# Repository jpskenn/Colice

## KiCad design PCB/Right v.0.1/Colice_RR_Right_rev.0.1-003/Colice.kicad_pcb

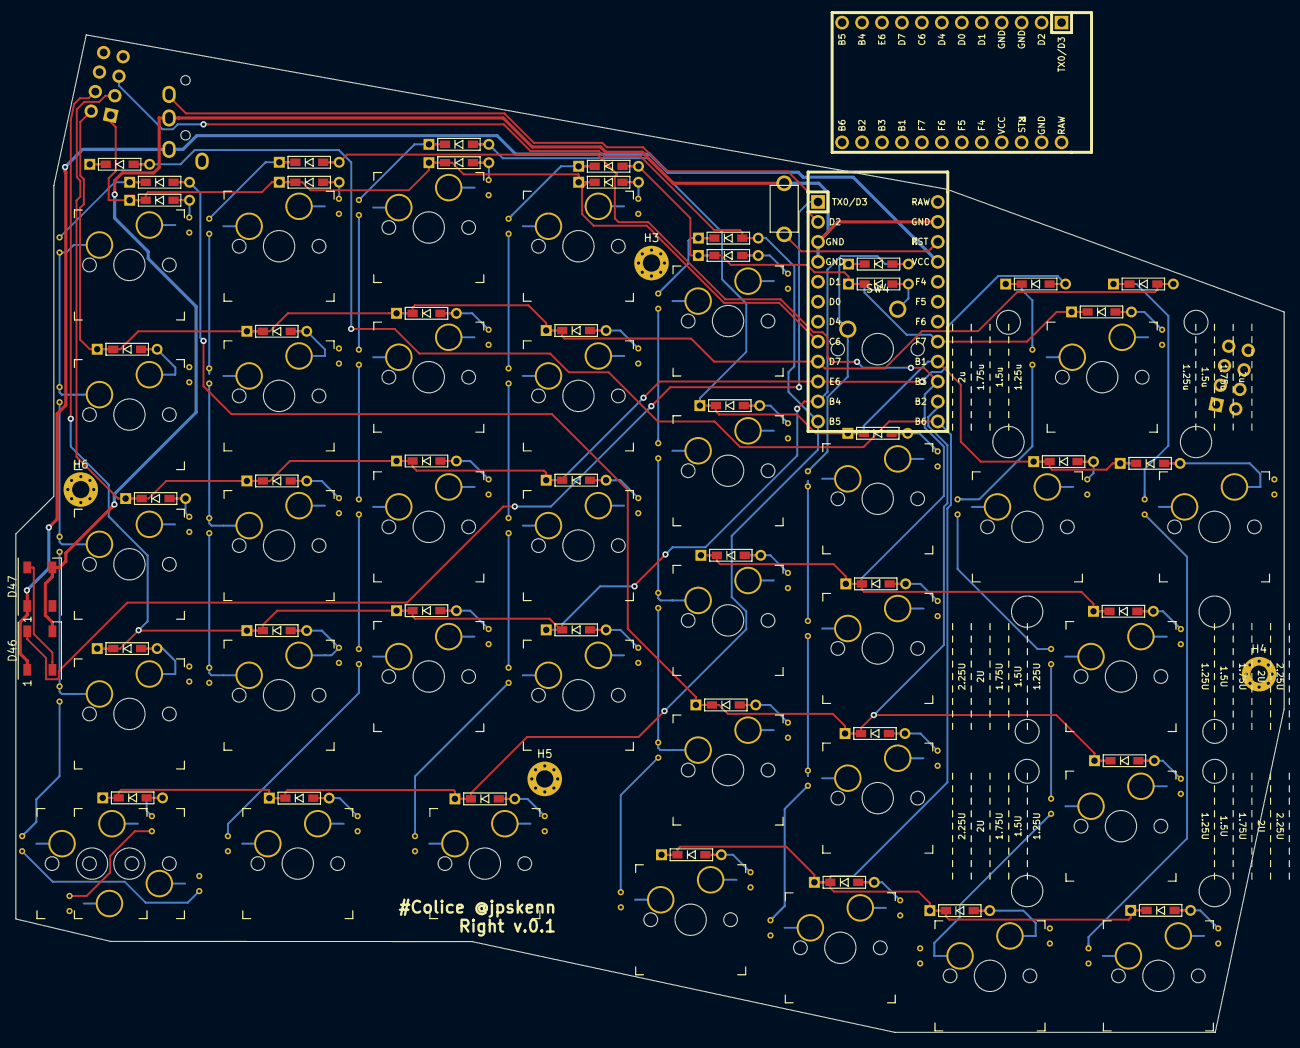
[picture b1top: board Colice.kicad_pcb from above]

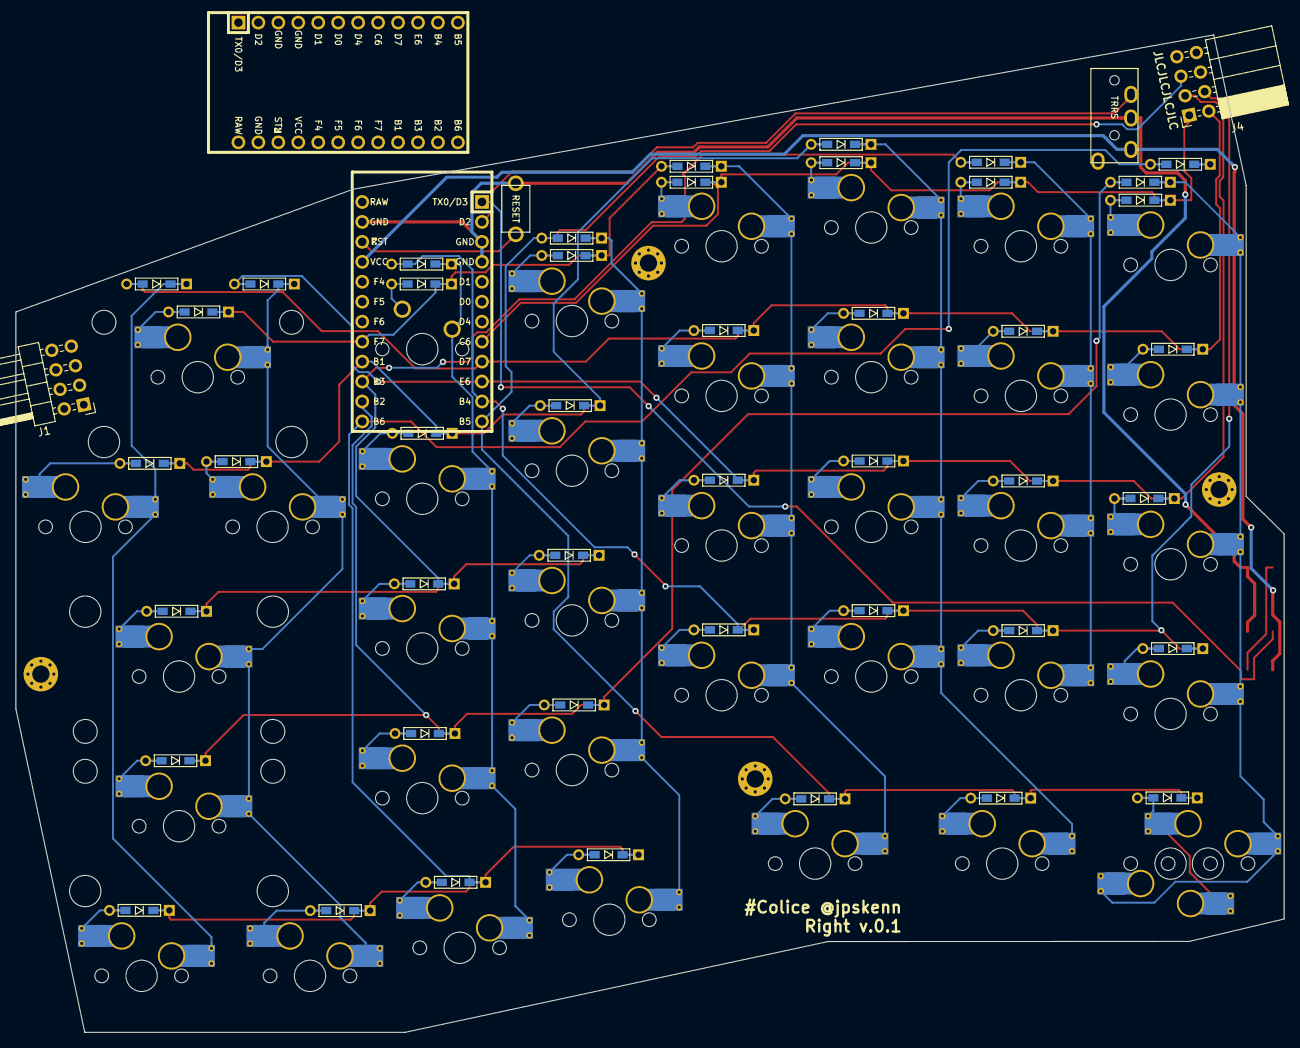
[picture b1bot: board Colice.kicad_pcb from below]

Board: 2 copper layers, 161.4 x 127.0 mm, 97 parts (5 on the bottom side), 60 nets.

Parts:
D1, D2, D3, D4, D5, D6, D7, D8, D9, D10, D11, D12, D13, D14, D15, D16, D17, D18, D19, D20, D21, D22, D23, D24, D25, D26, D27, D28, D29, D30, D31, D32, D34, D35, D36, D37, D38, D40, D45, D48, D49, D50, D51, D52, D53: D; D3_TH_SMD
D46, D47: WS2812B; LED_WS2812B_PLCC4_5.0x5.0mm_P3.2mm
H2: MountingHole; CherryMX_MidHeight_Choc_Hotswap_2U_Outline
H3, H4, H5, H6: MountingHole; MountingHole_2.2mm_M2_Pad_Via
H7, H8: MountingHole; CherryMX_MidHeight_Choc_Hotswap_2.25U_Outline
J1: Conn_02x04_Counter_Clockwise; PinHeader_2x04_P2.54mm_Horizontal
J3: MJ-4PP-9
J4: Conn_02x04_Counter_Clockwise; PinSocket_2x04_P2.54mm_Horizontal
SW1: SW_Push; ResetSW
SW3, SW5, SW6, SW7, SW8, SW9, SW10, SW11, SW12, SW14, SW15, SW16, SW17, SW18, SW19, SW20, SW21, SW22, SW23, SW24, SW25, SW26, SW27, SW29, SW30, SW31, SW32, SW33, SW38, SW39, SW40, SW41, SW42, SW43, SW44, SW45: SW_Push; CherryMX_Hotswap_v2
SW4: SW_Push; SW_Cherry_MX1A_1.00u_PCB
U1, U1#2: ProMicro; ArduinoProMicro

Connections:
GND1: D46.3, D47.3, J3.C, SW1.2, U1#2.3, U1#2.4, U1#2.23
unnamed: D1.1, SW3.1, SW41.1, SW42.1, SW43.1, SW44.1
unnamed: D2.2, SW41.2
unnamed: D3.2, SW3.2
unnamed: D4.1, SW4.1, SW5.1, SW6.1, SW7.1, SW8.1
unnamed: D5.2, SW4.2
unnamed: D6.2, SW5.2
unnamed: D7.2, SW6.2
unnamed: D8.2, SW7.2
unnamed: D9.2, SW8.2
unnamed: D10.1, SW9.1, SW10.1, SW11.1, SW12.1, SW45.1
unnamed: D11.2, SW9.2
unnamed: D12.2, SW10.2
unnamed: D13.2, SW11.2
unnamed: D14.2, SW12.2
unnamed: D15.1, SW39.1, SW40.1
unnamed: D16.1, SW14.1, SW15.1, SW16.1, SW17.1, SW18.1
unnamed: D17.2, SW14.2
unnamed: D18.2, SW15.2
unnamed: D19.2, SW16.2
unnamed: D20.2, SW17.2
unnamed: D21.2, SW18.2
unnamed: D22.1, SW19.1, SW20.1, SW21.1, SW22.1, SW23.1
unnamed: D23.2, SW19.2
unnamed: D24.2, SW20.2
unnamed: D25.2, SW21.2
unnamed: D26.2, SW22.2
unnamed: D27.2, SW23.2
unnamed: D28.1, SW24.1, SW25.1, SW26.1, SW27.1
unnamed: D29.2, SW24.2
unnamed: D30.2, SW25.2
unnamed: D31.2, SW26.2
unnamed: D32.2, SW27.2
unnamed: D34.1, SW29.1, SW30.1, SW31.1, SW32.1, SW33.1, SW38.1
unnamed: D35.2, SW29.2
unnamed: D36.2, SW30.2
unnamed: D37.2, SW31.2
unnamed: D38.2, SW32.2
unnamed: D45.2, SW33.2, SW38.2
unnamed: D46.2, D47.4
unnamed: D48.2, SW39.2
unnamed: D49.2, SW40.2
unnamed: D50.2, SW42.2
unnamed: D51.2, SW43.2
unnamed: D52.2, SW44.2
unnamed: D53.2, SW45.2
VCC: D46.1, D47.1, J3.D, U1#2.21
data: J3.B, U1#2.2
led: D46.4, U1#2.1
pin1: D2.1, D5.1, D11.1, D16.2, U1#2.17
pin2: D6.1, D12.1, D22.2, D48.1, D50.1, U1#2.16
pin3: D7.1, D13.1, D28.2, D51.1, U1#2.15
pin4: D8.1, D14.1, D34.2, D52.1, U1#2.14
pin5: D3.1, D9.1, D40.2, D49.1, D53.1, U1#2.13
pin6: D17.1, D23.1, D29.1, D35.1, J1.1, J4.1, U1#2.8
pin7: D15.2, D18.1, D24.1, D30.1, D36.1, J1.2, J4.2, U1#2.9
pin8: D1.2, D19.1, D25.1, D31.1, D37.1, J1.3, J4.3, U1#2.10
pin9: D4.2, D20.1, D26.1, D32.1, D38.1, J1.4, J4.4, U1#2.11
pin10: D10.2, D21.1, D27.1, D45.1, J1.5, J4.5, U1#2.12
reset: SW1.1, U1#2.22
